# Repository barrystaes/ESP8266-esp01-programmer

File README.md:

# ESP8266-esp01-programmer

This programmer for ESP8266-01 (ESP01) is not tested, yet.

## Schema:

## Board:

You can open these in Eagle.

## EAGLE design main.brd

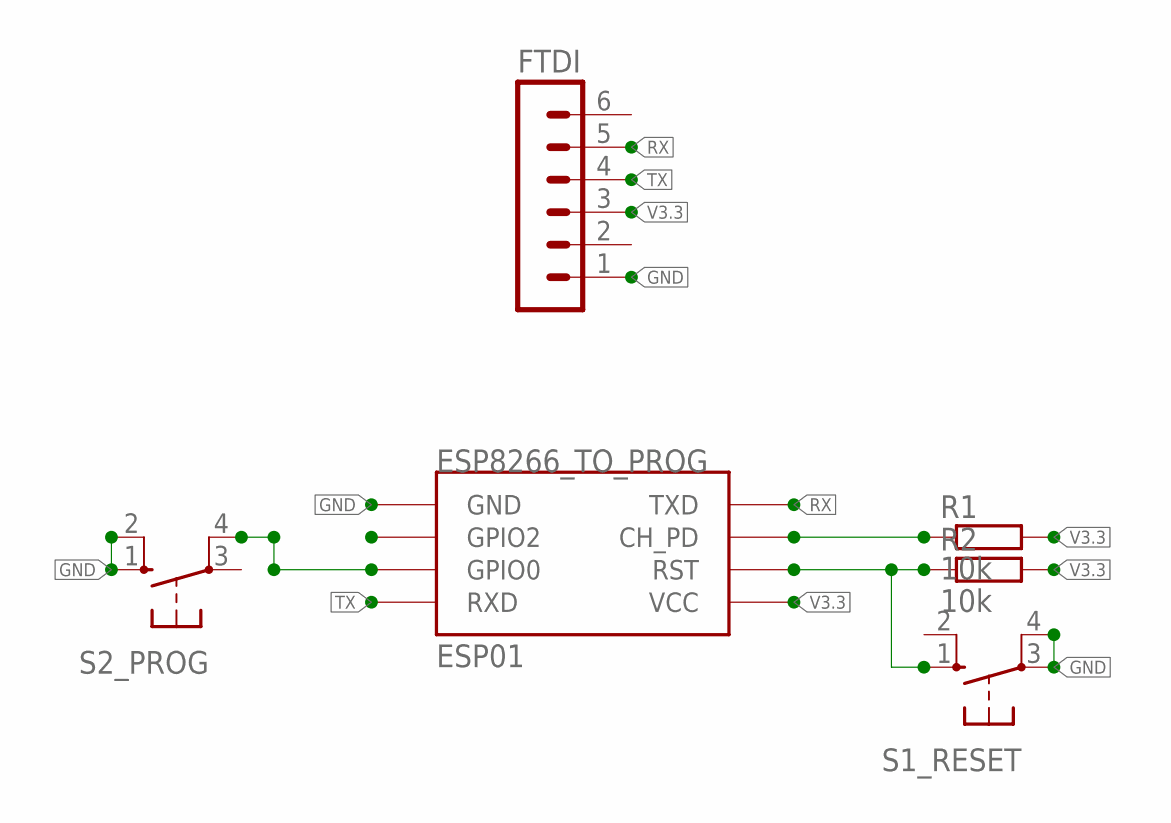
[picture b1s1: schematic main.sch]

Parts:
ESP8266_TO_PROG: ESP01
FTDI: MA06-1
R1, R2: 10k; 0204/7
S1_RESET, S2_PROG: 10-XX; B3F-10XX

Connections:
GND: ESP8266_TO_PROG.GND, FTDI.1, S1_RESET.3, S1_RESET.4 (P1), S2_PROG.1 (S), S2_PROG.2 (S1)
unnamed: ESP8266_TO_PROG.GPIO0, S2_PROG.4 (P1)
unnamed: ESP8266_TO_PROG.CH_PD, R1.1
unnamed: ESP8266_TO_PROG.RST, R2.1, S1_RESET.1 (S)
RX: ESP8266_TO_PROG.TX (TXD), FTDI.5
TX: ESP8266_TO_PROG.RX (RXD), FTDI.4
V3.3: ESP8266_TO_PROG.VCC, FTDI.3, R1.2, R2.2

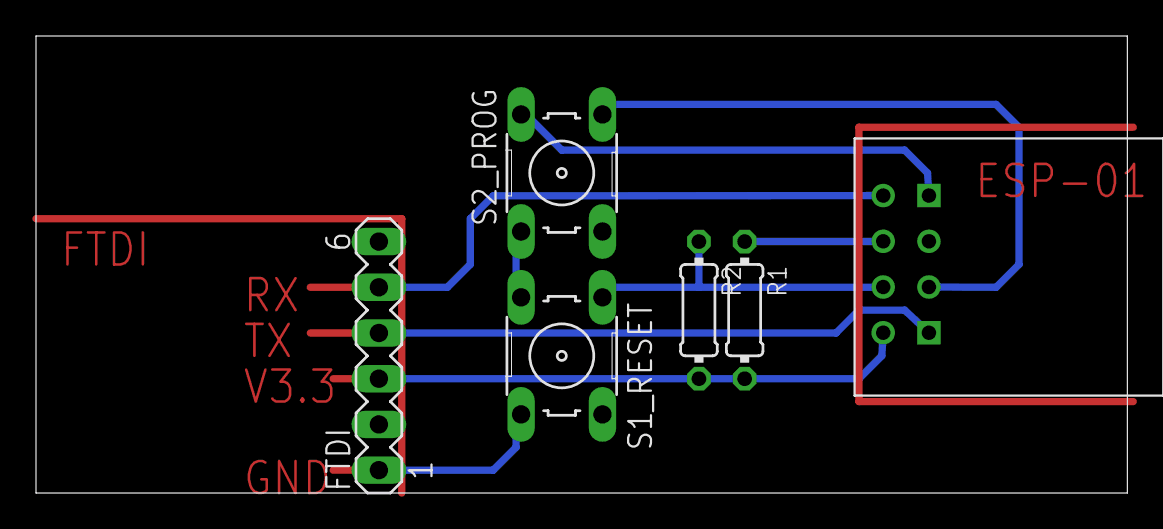
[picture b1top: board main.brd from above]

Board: 2 copper layers, 60.6 x 25.4 mm, 6 parts (0 on the bottom side), 7 nets.

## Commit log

2016-09-09 Initial commit.
2016-09-10 Test layout for proto PCB of 10x28 holes.
2016-09-10 Fix unused tracks, added R values.
2016-09-10 Board: FTDI placement, use 45 degrees corners, added text.
